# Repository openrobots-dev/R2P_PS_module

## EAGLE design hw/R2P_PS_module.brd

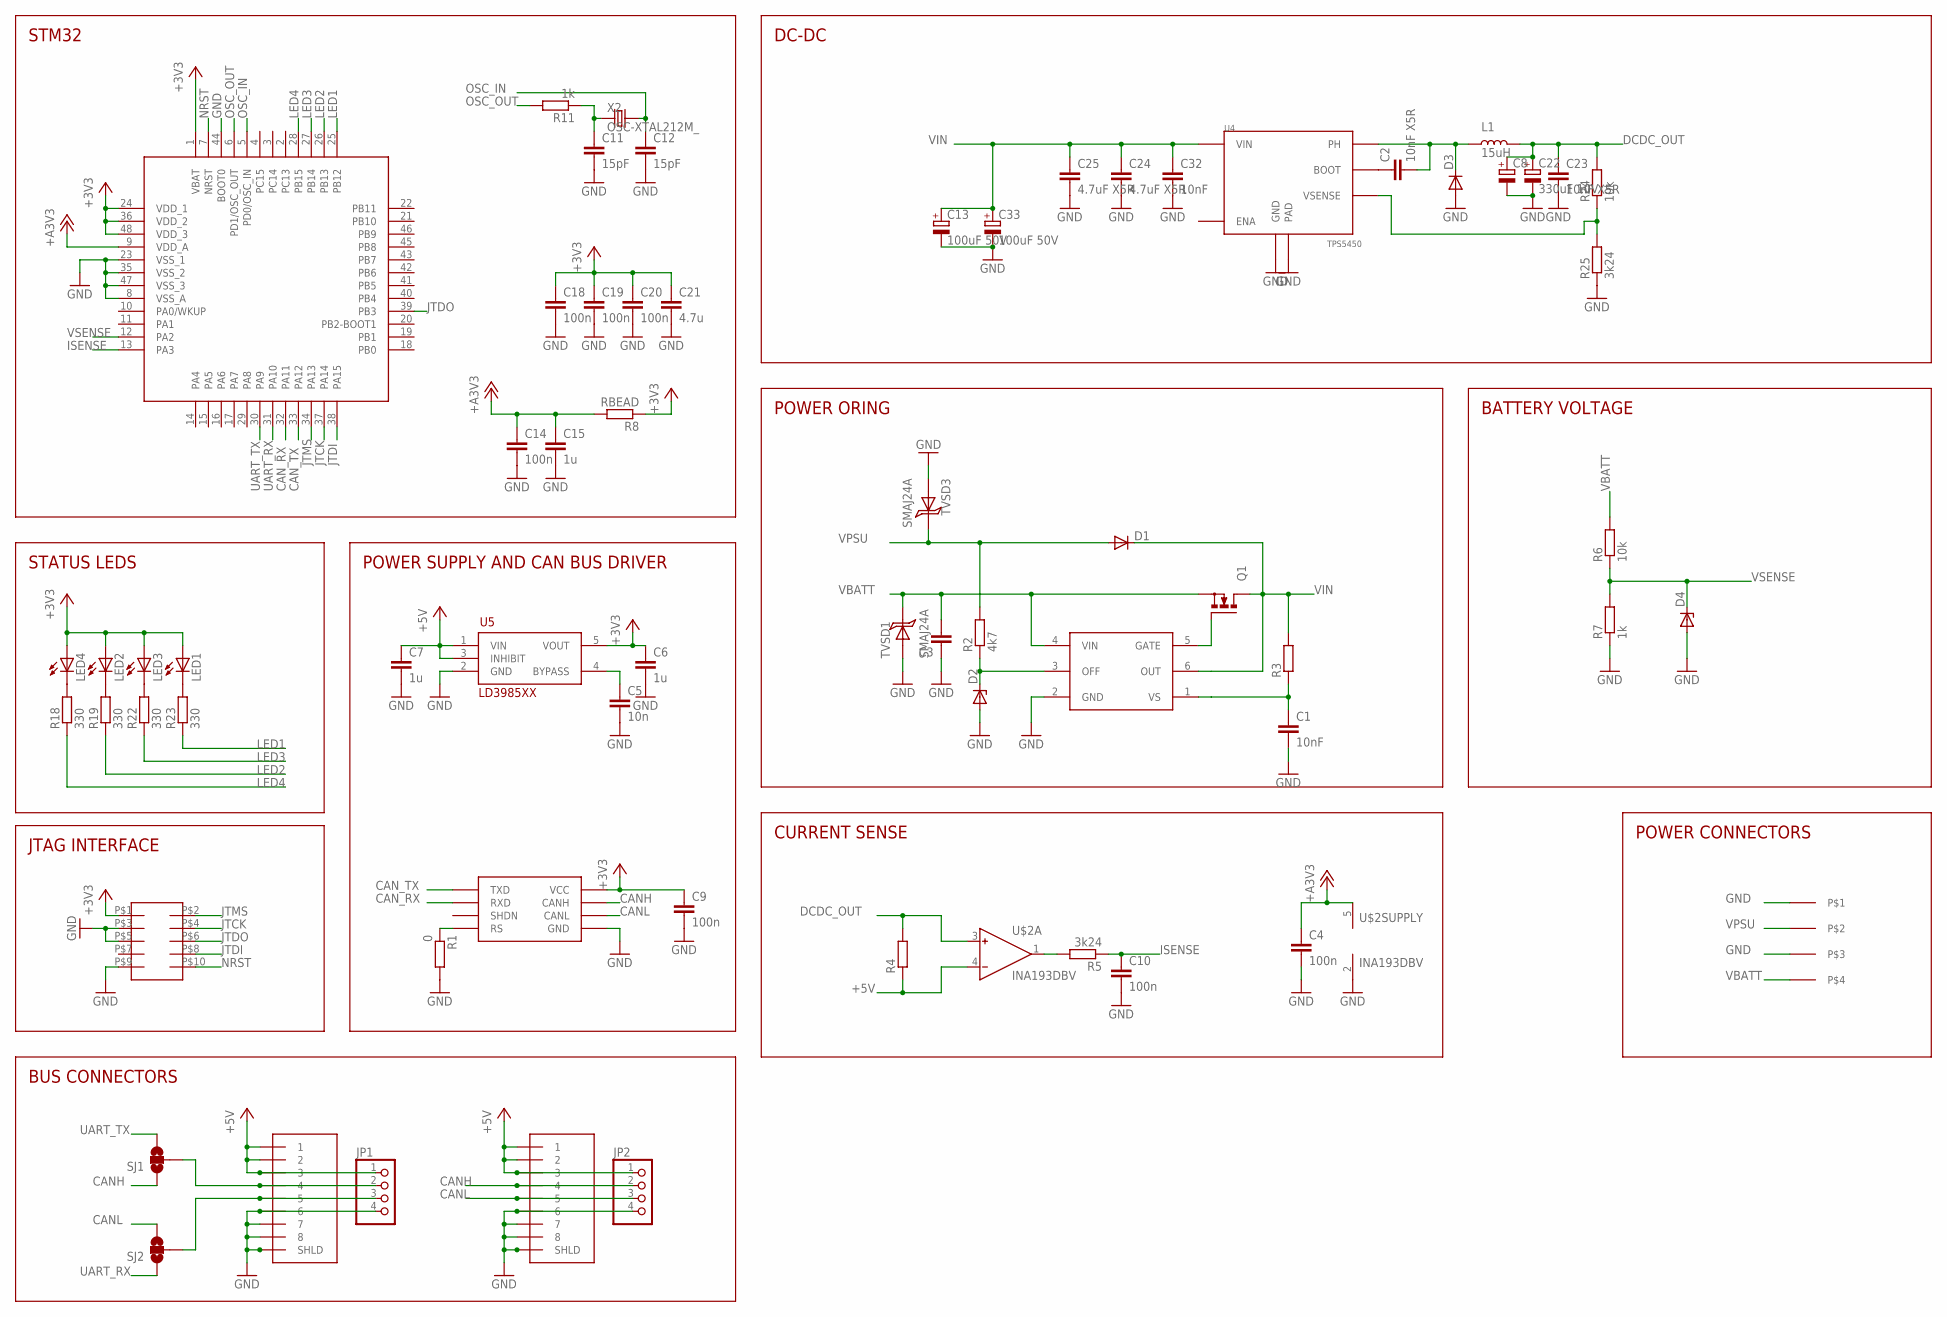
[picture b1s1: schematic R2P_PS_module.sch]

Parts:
1, 2: RJ45-43860; 0438600010
C1, C32: 10nF; C0603
C2, C23: 10nF X5R; C0603
C3: C-EUC0805; C0805
C4, C9, C10, C14, C18, C19, C20: 100n; C0603
C5: 10n; C0603
C6, C7, C15: 1u; C0603
C8: CPOL-EUE5-10.5; E5-10,5
C11, C12: 15pF; C0603
C13: 100uF 50V; E5-10,5
C21: 4.7u; C0805
C22: 330uF 10V; E2,5-7
C24, C25: 4.7uF X5R; C1210
C33: 100uF 50V; E2,5-7
D1, D3: DIODE-DO-214AC; DO-214AC
D2, D4: ZENERSOD-323F; SOD-323F
JP1, JP2: PINHD-1X4/90; 1X04/90
L1: 15uH; CDRH127
LED1, LED2, LED3, LED4: LEDCHIPLED_0805; CHIPLED_0805
Q1: N-MOSFET-SO8S; SO-08
R1: 0; R0603
R2: 4k7; R0603
R3: R-EU_R0603; R0603
R4: R-EU_R2512; R2512
R5, R25: 3k24; R0603
R6, R24: 10k; R0603
R7, R11: 1k; R0603
R8: RBEAD; R0603
R18, R19, R22, R23: 330; R0603
SJ1, SJ2: SOLDERJUMPER_2WAYPASTE1&2; SJ_3_PASTE1&2
SOT1: MAX3051; SOT23-8L
TVSD1, TVSD3: SMAJ24A; SMA
U1: STM32F103CX; LQFP48
U4: TPS5450; POWERPAD-SO8
U5: LD3985XX; SOT23-5L
U$1: LM5050-1; SOT23-6L
U$2: INA193DBV; SOT23-5L
U$3: POWERCONN-4
U$4: FTSH-105
X2: OSC-XTAL212M_; 4X6

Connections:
+3V3: C6.1, C9.1, C18.1, C19.1, C20.1, C21.1, LED1.A, LED2.A, LED3.A, LED4.A, R8.1, SOT1.P$3 (VCC), U1.1 (VBAT), U1.24 (VDD_1), U1.36 (VDD_2), U1.48 (VDD_3), U5.5 (VOUT), U$4.P$1
+5V: 1.P$1 (1), 1.P$2 (2), 1.P$3 (3), 2.P$1 (1), 2.P$2 (2), 2.P$3 (3), C7.1, JP1.1, JP2.1, R4.1, U5.1 (VIN), U5.3 (INHIBIT), U$2.4 (IN-)
+A3V3: C4.1, C14.1, C15.1, R8.2, U1.9 (VDD_A), U$2.5 (V+)
CANH: 2.P$4 (4), JP2.2, SJ1.1, SOT1.P$7 (CANH)
CANL: 2.P$5 (5), JP2.3, SJ2.3, SOT1.P$6 (CANL)
CAN_RX: SOT1.P$4 (RXD), U1.32 (PA11)
CAN_TX: SOT1.P$1 (TXD), U1.33 (PA12)
DCDC_OUT: C8.+, C22.+, C23.1, L1.P$2 (2), R4.2, R24.2, U$2.3 (IN+)
GND: 1.P$6 (6), 1.P$7 (7), 1.P$8 (8), 1.P$9 (SHLD), 1.P$10, 2.P$6 (6), 2.P$7 (7), 2.P$8 (8), 2.P$9 (SHLD), 2.P$10, C1.2, C3.1, C4.2, C5.2, C6.2, C7.2, C8.-, C9.2, C10.2, C11.2, C12.2, C13.-, C14.2, C15.2, C18.2, C19.2, C20.2, C21.2, C22.-, C23.2, C24.2, C25.2, C32.2, C33.-, D2.A, D3.A, D4.A, JP1.4, JP2.4, R1.2, R7.1, R25.1, SOT1.P$2 (GND), TVSD1.A, TVSD3.A, U1.8 (VSS_A), U1.23 (VSS_1), U1.35 (VSS_2), U1.44 (BOOT0), U1.47 (VSS_3), U4.P6 (GND), U4.PAD, U5.2 (GND), U$1.2 (GND), U$2.2 (V-), U$3.P$1, U$3.P$3, U$4.P$3, U$4.P$5, U$4.P$9
ISENSE: C10.1, R5.1, U1.13 (PA3)
JTCK: U1.37 (PA14), U$4.P$4
JTDI: U1.38 (PA15), U$4.P$8
JTDO: U1.39 (PB3), U$4.P$6
JTMS: U1.34 (PA13), U$4.P$2
LED1: R23.1, U1.25 (PB12)
LED2: R19.1, U1.26 (PB13)
LED3: R22.1, U1.27 (PB14)
LED4: R18.1, U1.28 (PB15)
unnamed: R1.1, SOT1.P$8 (RS)
unnamed: 1.P$4 (4), JP1.2, SJ1.2
unnamed: C5.1, U5.4 (BYPASS)
unnamed: D2.C, R2.1, U$1.3 (OFF)
unnamed: Q1.4 (G), U$1.5 (GATE)
unnamed: 1.P$5 (5), JP1.3, SJ2.2
unnamed: C1.1, R3.1, U$1.1 (VS)
unnamed: C11.1, R11.1, X2.1 (X1)
unnamed: R5.2, U$2.1 (OUT)
unnamed: LED4.C, R18.2
unnamed: LED2.C, R19.2
unnamed: LED3.C, R22.2
unnamed: LED1.C, R23.2
unnamed: C2.1, U4.P1 (BOOT)
unnamed: R24.1, R25.2, U4.P4 (VSENSE)
NRST: U1.7 (NRST), U$4.P$10
OSC_IN: C12.1, U1.5 (PD0/OSC_IN), X2.2 (X2)
OSC_OUT: R11.2, U1.6 (PD1/OSC_OUT)
PH: C2.2, D3.C, L1.P$1 (1), U4.P8 (PH)
UART_RX: SJ2.1, U1.31 (PA10)
UART_TX: SJ1.3, U1.30 (PA9)
VBATT: C3.2, Q1.1 (S), Q1.2 (S), Q1.3 (S), R6.2, TVSD1.C (K), U$1.4 (VIN), U$3.P$4
VIN: C13.+, C24.1, C25.1, C32.1, C33.+, D1.C, Q1.5 (D), Q1.6 (D), Q1.7 (D), Q1.8 (D), R3.2, U4.P7 (VIN), U$1.6 (OUT)
VPSU: D1.A, R2.2, TVSD3.C (K), U$3.P$2
VSENSE: D4.C, R6.1, R7.2, U1.12 (PA2)

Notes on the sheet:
STM32
POWER SUPPLY AND CAN BUS DRIVER
STATUS LEDS
JTAG INTERFACE
DC-DC
BUS CONNECTORS
POWER CONNECTORS
POWER ORING
BATTERY VOLTAGE
CURRENT SENSE

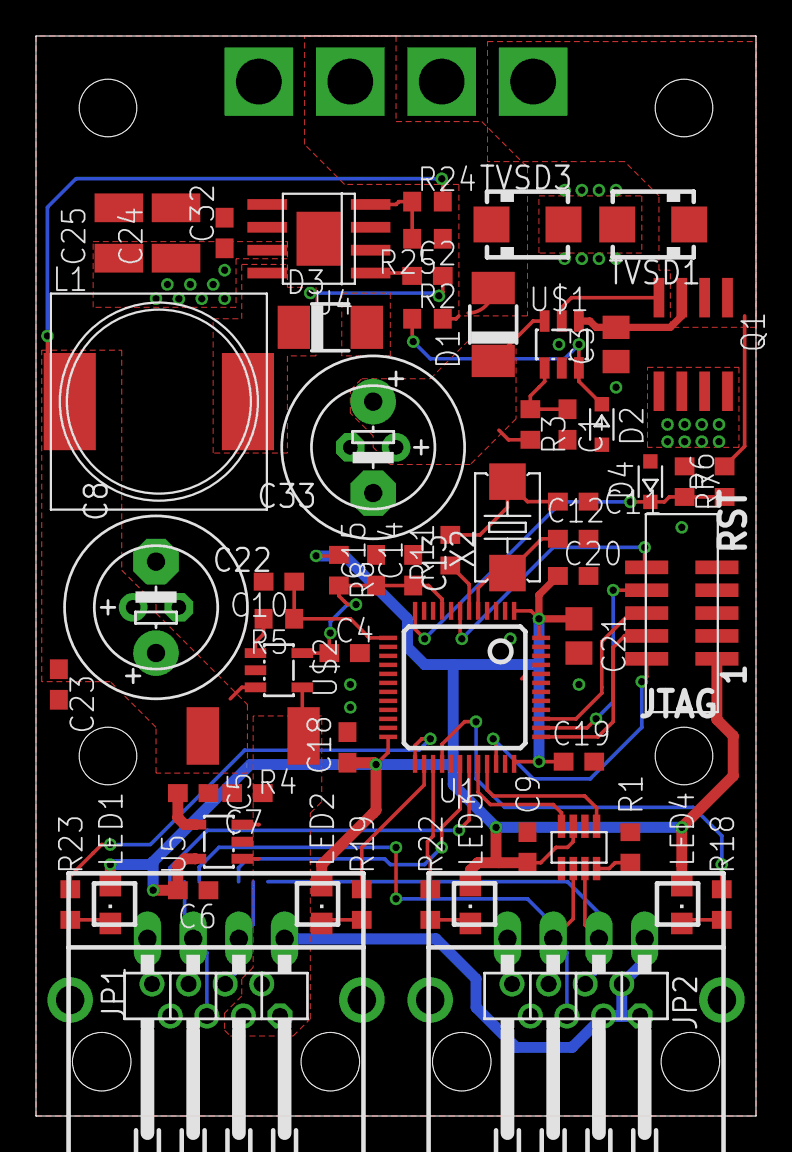
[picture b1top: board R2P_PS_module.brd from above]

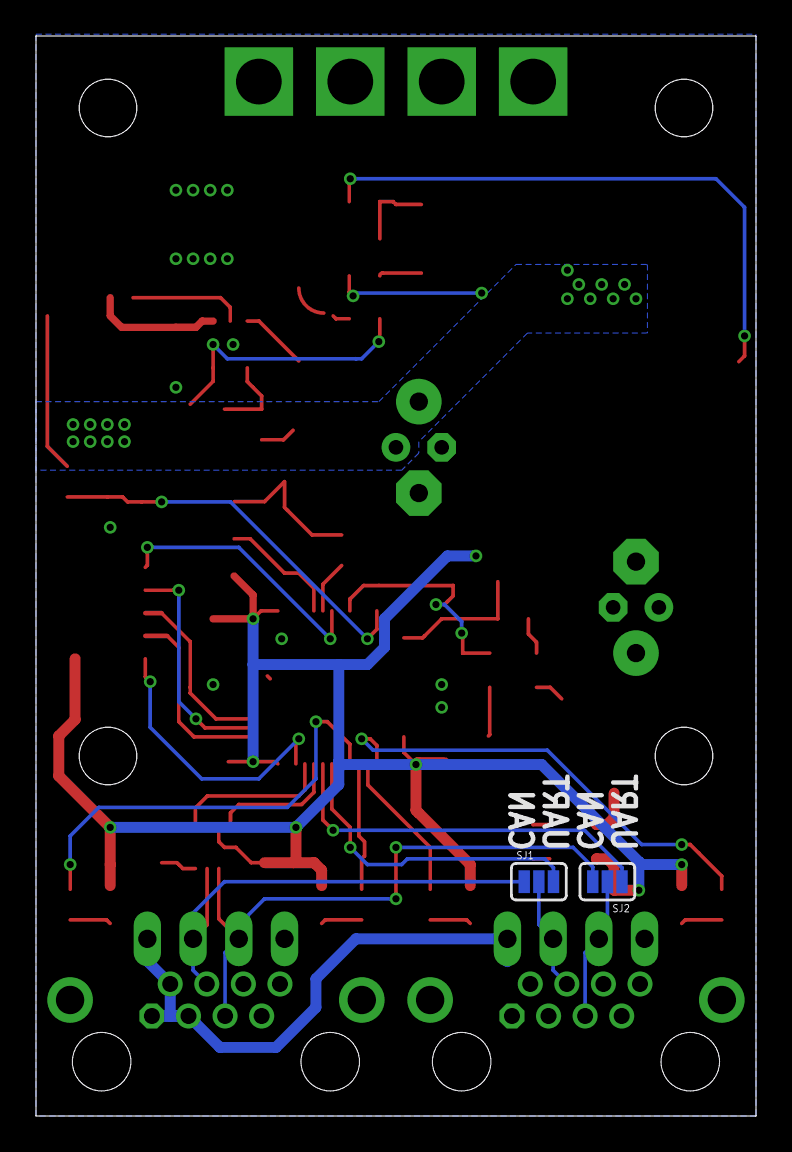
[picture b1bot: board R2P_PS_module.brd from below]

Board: 2 copper layers, 40.0 x 60.0 mm, 67 parts (2 on the bottom side), 43 nets.

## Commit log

2012-07-24 Schematics and board layout first commit
2012-07-24 Moved schematics and board layout under eagle directory
2012-07-24 Removed some files
2012-07-30 Datasheets added
2012-07-30 .gitignore added to revision control
2012-08-28 Update MCU layout
2013-08-01 Added R2 value
2013-11-29 added missing component values
2014-07-08 demo setup
